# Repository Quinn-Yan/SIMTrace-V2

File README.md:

# Osmocom SIMtrace

(C) 2010-2017 by Harald Welte <laforge@gnumonks.org>

SIMTtraceis a program that can be used for tracing the communication
between a phone and the SIM card.  More generally, it can trace any
ISO 7816 based smart card interface.

SIMtrace is part of the [Osmocom](https://osmocom.org/) Open Source
Mobile Communications project.

This repository contains a host program 'simtrace' as well as a patch
for wireshark (which is part of mainline wireshark since February 2012)

The corresponding device firmware source code can be found at
<http://git.osmocom.org/openpcd/>

## Homepage

The official homepage of the project is
<https://osmocom.org/projects/simtrace/wiki/>

GIT Repository
--------------

You can clone from the official simtrace.git repository using

	git clone git://git.osmocom.org/simtrace.git

There is a cgit interface at <http://git.osmocom.org/simtrace/>

## Documentation

There is a PDF user manual available from
<https://osmocom.org/attachments/download/2139/usermanual.pdf>

Mailing List
------------

Discussions related to simtrace are happening on the
simtrace@lists.osmocom.org mailing list, please see
<https://lists.osmocom.org/mailman/listinfo/simtrace> for subscription
options and the list archive.

Please observe the [Osmocom Mailing List
Rules](https://osmocom.org/projects/cellular-infrastructure/wiki/Mailing_List_Rules)
when posting.

Contributing
------------

Our coding standards are described at
<https://osmocom.org/projects/cellular-infrastructure/wiki/Coding_standards>

We us a e-mail based patch submission/review process on the
above-mentioned mailing list for contributions.

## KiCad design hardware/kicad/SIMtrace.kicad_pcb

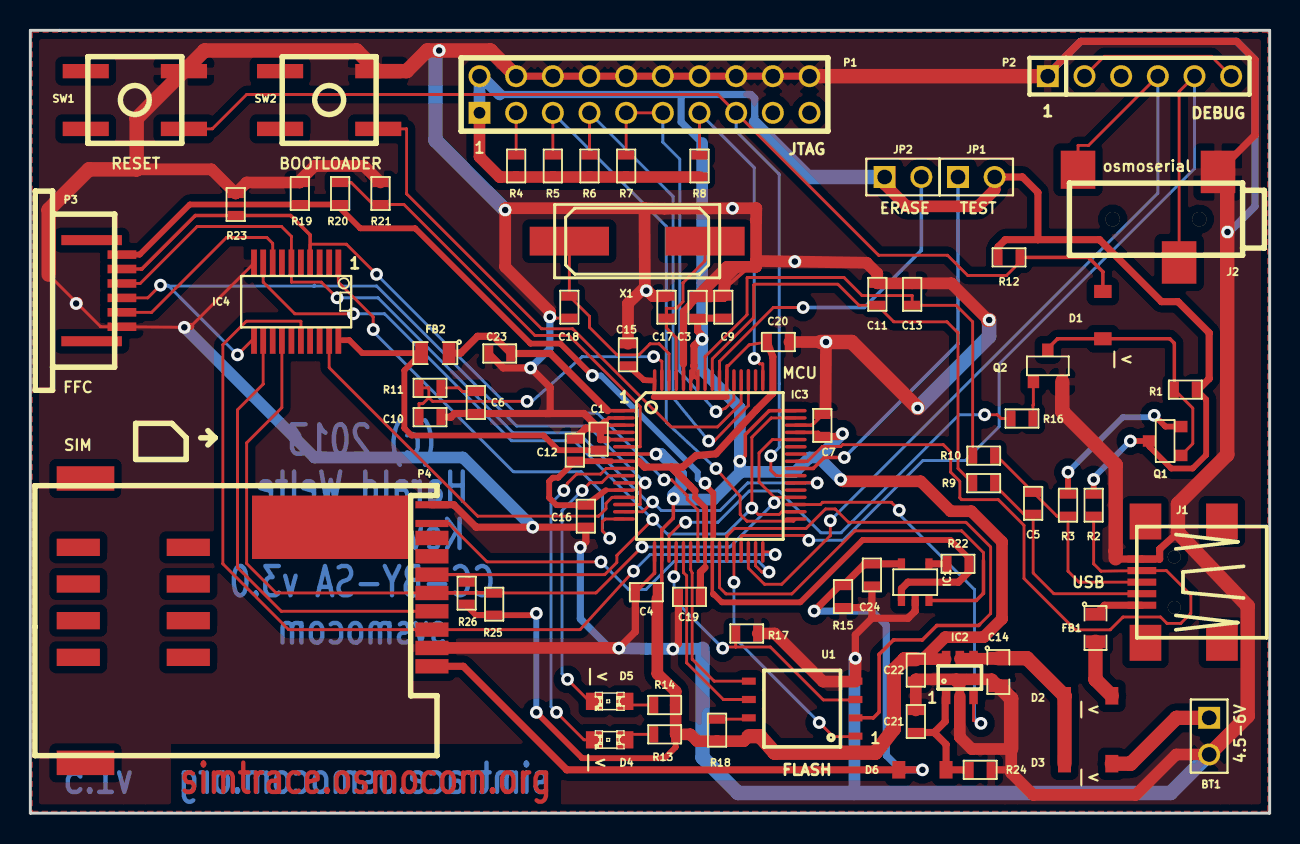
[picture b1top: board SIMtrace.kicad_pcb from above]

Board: 2 copper layers, 85.9 x 54.2 mm, 75 parts (0 on the bottom side), 61 nets.

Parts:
BT1: 4.5-6V; PIN_ARRAY_2X1
C1, C12: 2.2uF; SM0603
C3, C4, C7, C9, C15, C16, C19, C20, C23, C24: 100nF; SM0603
C5: 33pF; SM0603
C6: 10nF; SM0603
C10: 1nF; SM0603
C11, C13: 15pF; SM0603
C14: 4.7uF; SM0805
C17, C18: 10pF; SM0603
C21, C22: 1uF; SM0603
D1, D2, D3, D6: MBR0530; SOD123
D4: RED; LED-0805
D5: GREEN; LED-0805
FB1, FB2: FILTER; SM0805
IC1: FPF2109; SOT23-5
IC2: AP7332; SOT26
IC3: MCU; TQFP_64
IC4: CB3Q3244; SSOP20_BDQ
J1: USB; USB-MINI-B_UX60
J2: osmoserial; JACK_2.5
JP1: TEST; PIN_ARRAY_2X1
JP2: ERASE; PIN_ARRAY_2X1
P1: JTAG; PIN_ARRAY_10X2
P2: DEBUG; PIN_ARRAY-6X1
P3: FFC; FFC_REBELSIM
P4: SIM; SIM_AMPHENOL
Q1, Q2: BC847; SOT23_BC847
R1, R4, R5, R6, R7, R8, R12, R15, R19, R22, R23, R24, R25, R26: 100K; SM0603
R2, R16, R17, R18: 10K; SM0603
R3, R11: 1K5; SM0603
R9, R10: 27R; SM0603
R13, R14: 150R; SM0603
R20, R21: 10k1%; SM0603
SW1: RESET; PUSH_BUTTON
SW2: BOOTLOADER; PUSH_BUTTON
U1: FLASH; SOC008_WIDE
X1: 18.432MHz; Q_49U3HMS

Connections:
3V3: C1.1, C3.1, C4.1, C7.1, C9.1, C22.1, FB2.2, IC2.6, IC3.7, IC3.18, IC3.45, IC3.48, IC3.58, IC3.59, IC4.20, JP1.2, JP2.1, P1.1, P1.2, Q1.3, R1.1, R2.2, R4.2, R5.2, R6.2, R7.2, R8.2, R12.1, R13.1, R14.1, R18.2, R25.1, R26.1, U1.8
+1.8V: C12.1, C15.1, C16.1, C19.1, C20.1, IC3.8, IC3.12, IC3.24, IC3.54, IC3.64
//RESET: D1.1, IC3.39, P1.15, R12.2, SW1.1
/A-B-DETECT: IC3.41, J1.4, R2.1
/BOOTLOADER: IC3.52, SW2.1
/CLK_PHONE: IC3.15, IC3.38, IC4.6, P3.3
/CLK_SIM: IC3.36, IC3.44, IC4.14, P4.C3, R25.2
/CS: IC3.28, U1.1
/DDM: C11.1, IC3.56, R9.1
/DDP: C13.1, IC3.57, R10.1
/DRXD: IC3.30, J2.2, P2.4
/DTXD: IC3.29, J2.3, P2.5
/I/O_PHONE: IC3.11, IC3.14, IC4.11, P3.4
/I/O_SIM: IC3.34, IC3.47, IC4.9, P4.C7, R26.2
/I/O_SW: IC3.13, IC4.19
/LED_G: D5.2, IC3.10
/LED_R: D4.2, IC3.9
/MISO: IC3.27, U1.2
/MOSI: IC3.22, U1.5
/RST_PHONE: IC3.23, IC4.4, P3.2, R23.2
/RST_SIM: IC3.32, IC4.16, P4.C2
/SCK: IC3.21, U1.6
/SC_SW: IC3.16, IC4.1
/SIM_PWEN: IC2.3, IC3.35
/SW_SIM: IC3.31, P4.SW1
/TCK: IC3.53, P1.9, P1.11, R7.1
/TDI: IC3.33, P1.5, R5.1
/TDO: IC3.49, P1.13, R8.1
/TEST: IC3.40, JP1.1
/TMS: IC3.51, P1.7, R6.1
/UDP_PUP: D1.2, Q1.1, Q2.3, R1.2
/USBVCC: D2.2, FB1.2
/VCC_FWD: IC1.3, IC3.26
/VCC_PHONE: IC1.1, IC3.25, P3.1, R19.2, R20.1, R22.1
/VCC_SIM: C24.1, D6.1, IC1.5, P4.C1, R15.1
/VPP_PHONE: IC4.8, P3.5
/VPP_SIM: IC4.12, P4.C6
/WP: IC3.20, R17.1, U1.3
GND: BT1.2, C1.2, C3.2, C4.2, C6.1, C7.2, C9.2, C10.1, C11.2, C12.2, C13.2, C14.2, C15.2, C16.2, C17.2, C18.2, C19.2, C20.2, C21.2, C22.2, C23.2, C24.2, IC1.2, IC2.2, IC3.2, IC3.3, IC3.4, IC3.5, IC3.17, IC3.46, IC3.60, IC4.10, J1.5, J2.1, P1.4, P1.6, P1.8, P1.10, P1.12, P1.14, P1.16, P1.18, P1.20, P2.1, P3.6, P4.C5, P4.SW2, Q2.2, R15.2, R17.2, R19.1, R21.1, R23.1, R24.2, SW1.2, SW2.2, U1.4
unnamed: R18.1, U1.7
unnamed: Q2.1, R16.1
unnamed: C14.1, D2.1, D3.1, IC2.4, IC2.5
unnamed: IC3.6, R20.2, R21.2
unnamed: Q1.2, R3.2
unnamed: C5.2, J1.3, R3.1, R10.2
unnamed: P2.2, P2.6
unnamed: IC3.55, JP2.2
unnamed: IC3.19, R16.2
unnamed: C18.1, IC3.62, X1.2
unnamed: IC1.4, R22.2
unnamed: BT1.1, D3.2
unnamed: C21.1, D6.2, IC2.1, R24.1
unnamed: C6.2, R11.2
unnamed: P1.3, R4.1
unnamed: C17.1, IC3.61, X1.1
unnamed: C10.2, IC3.63, R11.1
unnamed: D5.1, R14.2
unnamed: D4.1, R13.2
unnamed: C5.1, J1.2, R9.2
unnamed: FB1.1, J1.1
unnamed: C23.1, FB2.1, IC3.1

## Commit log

2011-07-02 schottky STPS340U replaces MBR0530T1 for production. datasheet added
2011-07-02 flash memory S25FL016A replaces SST25VF040B for production. datasheet added
2011-07-02 footprints for flash S25FL016A and schottky STPS340U created
2011-07-02 new footprints select for production in netlist (LED is 0805, schottky is SMB_STPS340U, flash is SO008_wide
2011-07-02 board adapted to new footprints
2011-07-02 PS/gerber rendered for production
2011-07-02 BOM updated for production
2011-07-02 D2 and D3 now also use STPS340U instead of 1N5819
2011-07-02 v1.0p corrected and rendered. BOM updated
2011-07-14 make: Create a very simple install target.
2011-07-14 misc: Copy the simtrace_usb.h file here. no symlink for debian
2011-07-14 debian: Attempt to package the SIMtrace
2011-07-15 debian: Fix dependency and installation
2011-11-01 ftdi 3.3v cut in schema
2011-11-03 footprint refreched, cap near LDO
2011-11-03 +1.8V line enlarged on C12, C15, C16. not possible on C19
2011-11-05 VPP connected through bus switch
2011-11-05 hw: solder mask between at91sam7s added
2011-11-05 hw: sysmocom added to copper, gerber rendered
2011-11-14 hw: final SIMtrace v1.1 board rendering
2011-12-05 hw: fabrication output generated
2012-05-15 SIMtrace: Improve PCB routing of GND, 3V3 and VCC traces
    We have to make sure the impedance of the supply lanes is not too high.
    Particularly bad was passing GND in 0.2mm under several resistors before
    even reaching the LDO from the USB socket.
    This attempts to address the major issues. Also, the input capacitor is
    moved closer to the LDO once again
2012-05-15 DRC rules violations corrected
2012-05-16 C14 change to 4.7uF 0805, silkscreen improved, more space for JTAG
2012-05-16 v1.2p fabrication exported
2012-05-17 Add R23 (pull-up for !SIM_RST signal)
    While the SAM7 has an internal pull-up, this is of no use if the bus
    switch input is left open and collects noise resulting in bogus nRST
    interrupts.
2012-05-18 RST_PHONE pulldown added on PCB
2012-05-19 Mark IC5 as "do not place" (VCC_Forward) as it doesn't work anyway
    If the LDO is switched off, then even if we try to forward power from
    the phone to the SIM, the current will sink inside the LDO (no reverse
    current protection).
2013-10-27 added FPF210X symbol to library
2013-10-27 v1.3 modifications: replaced IC switch with FPF2109, added schottky and pull-down resistors
2013-10-27 exported v1.3 netlist
2013-10-27 set footprints to symbols
2013-10-27 new KiCAD layout format, silkscreen refdes 0.5mm, text 0.75mm, new components loaded
2013-10-27 MBR0530 pin numbers corrected
2013-10-27 new components placed and routed
2013-10-27 exported fabrication files
2013-10-27 MCU pin 48 used to identify v1.3 by putting it to ground (with internal pull-up)
2013-10-27 re-add BOM spreadsheet with updated v1.3 components
2013-10-28 BOM corrected (sorted by value) and reformated
2013-11-11 simtrace 1.3: move point of origin to lower left corner of PCB
2013-11-16 add datasheet of SPI flash component mounted on recent boards
    At some point during v1.2p production, we switched from the S25FL016
    to the S25FL032P SPI flash model. v1.3 all have that flash (so far).
2014-04-26 add PCB design of mini-UICC (original and reverse) adapters
2014-04-30 mini-UICC-reverse: re-generate gerber and add outline GBR
2014-06-20 Schematic: Make sure PA0 to PA2 are high on power-up
    any other level is interfering with SAM-BA operation. This fixes
    the PA0=GND bug in the previous v1.3 version.
2014-06-20 v1.4: Connect PA0 to 3V3; pull-up for PA1/PA2 (R25,R26)
    PA0, PA1 and PA2 must be high during reset to enter SAM-BA mode.
2014-06-23 export schematic, and pcb (with minor esthetic corrections)
2014-06-26 Update BOM for v1.4
    * AT91SAM128D, not C, as old is EOL
    * New ferrite bead / filter, as old is EOL.
    * Flash S25FL032P0XMFI011, was already populated in v1.3
2015-07-05 change microcontroller to SAM3S
2015-08-19 Add 4FF (nanoSIM) adapter
2016-04-01 remove second copy of mini-UICC FPC adapter
2016-04-01 add 'sysmocom' name to mini-UICC and nano-UICC adapters
    As sysmocom is the only company manufacturing them for now, we add this
    branding to the design files.
2017-03-17 update README with current information + convert to Markdown

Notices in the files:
hardware/kicad/SIMtrace.kicad_pcb:
CC-BY-SA v3.0 unported
(c) 2013
CC-BY-SA v3.0
